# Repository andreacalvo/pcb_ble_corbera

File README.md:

## BLE Corbera

Kicad design, BLE Temperature Humidity sensor

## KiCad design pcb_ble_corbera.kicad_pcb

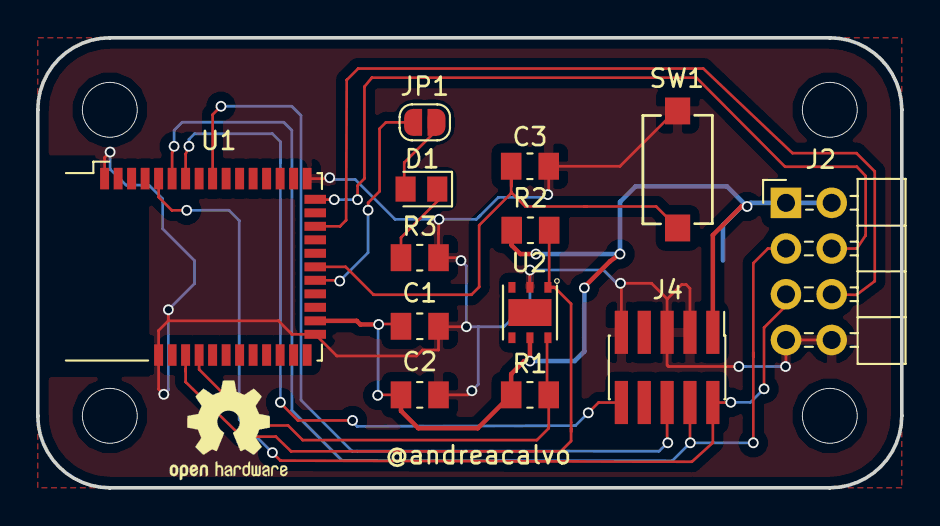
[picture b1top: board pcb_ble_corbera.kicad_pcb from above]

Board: 2 copper layers, 48.0 x 25.0 mm, 14 parts (1 on the bottom side), 14 nets.

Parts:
C1: 0.1uF, 16V; C_0805_2012Metric_Pad1.15x1.50mm_HandSolder
C2: 100nF; C_0805_2012Metric_Pad1.15x1.50mm_HandSolder
C3: 104pF; C_0805_2012Metric_Pad1.15x1.50mm_HandSolder
D1: LED; LED_0805_2012Metric_Pad1.12x1.40mm_HandSolder
J1: Battery_Cell; Keystone_1058_1x2032-CoinCell
J2: Conn_02x04_Odd_Even; PinHeader_2x04_P2.54mm_Horizontal_No_Pins
J4: Conn_ARM_JTAG_SWD_10; PinHeader_2x05_P1.27mm_Vertical_SMD
JP1: SolderJumper_2_Open; SolderJumper-2_P1.3mm_Open_RoundedPad1.0x1.5mm
R1, R2: 5.7k; R_0805_2012Metric_Pad1.15x1.50mm_HandSolder
R3: 220R; R_0805_2012Metric_Pad1.15x1.50mm_HandSolder
SW1: SW_Push; SW_SMD_60X3.8
U1: BL652; Laird_BL652
U2: SHT20

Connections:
BUTTON_0: C3.1, SW1.2, U1.22
GND: C1.2, C2.2, C3.2, J1.2, J2.7, J2.8, J4.3, J4.5, J4.9, R3.2, SW1.1, U1.1, U1.16, U1.27, U1.39, U2.2
LED_0: JP1.2, U1.23
unnamed: D1.1, R3.1
unnamed: D1.2, JP1.1
RESET: J4.10, U1.7
SCL: R1.1, U1.36, U2.6
SDA: R2.1, U1.37, U2.1
SERIAL_RX: J2.6, U1.19
SERIAL_TX: J2.4, U1.17
SIO_18: J4.6, U1.9
SWDCLK: J2.3, J4.4, U1.6
SWDIO-TMS: J2.5, J4.2, U1.5
VCC: C1.1, C2.1, J1.1, J2.1, J2.2, J4.1, R1.2, R2.2, U1.26, U2.5

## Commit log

2018-04-15 added README
2018-04-15 added bl652 and hdc1080 3D models
2018-04-16 added debug connector to the schematic
2018-04-17 New page + BLE652 pins labels
2018-04-17 New page + connectors interface
2018-04-18 Global variables BL652 + 18 conectors
2018-04-18 updated 18 pin connector
2018-04-18 removed 2x18 pin connector from BL652 sheet
2018-04-18 tweaks for pcb layout
2018-04-20 reduced schematic, no header connectors
2018-04-23 changed battery, switch, debug conn
2018-04-24 new tracks
2018-04-26 layout 90%
2018-04-27 updates..
2018-04-28 added texts
2018-04-28 changed battery holder
2018-04-28 added battery holder 3d model
2018-04-28 changed battery holder in sch
2018-05-14 changed hdc1080 with sht20
2018-05-15 added kicad logo

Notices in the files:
pcb_ble_corbera.kicad_pcb:
ραυηεт©2018
